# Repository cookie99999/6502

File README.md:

These are the relevant files for my ongoing WDC 65C816 based homebrew computer. It started off pretty similar to Ben Eater's 65C02 computer, but I've made significant changes since then and will continue to do so.

## Current Specs:
- WDC 65C816 clocked at 4MHz (reasonably stable at 6MHz, fails to boot at 8 likely due to slow memory/logic)
- 512K SRAM
- 8K NOR flash accessible to the user
- 2 6522 VIAs providing 2 8-bit GPIO ports and a couple timers and shift registers each
- 6551 ACIA UART for serial I/O. Rockwell part works only up to about 4MHz, but avoids the TX empty flag bug of the WDC part
- PS/2 interface provided by ATTiny26L on one of the VIA ports
- CompactFlash storage (via PATA adapter)
- VGA video output from a Pi Pico 2 providing text display and (very slow) bitmapped graphics
- expensive and oversized 4-layer PCB

## To do list:
- Bitbang an SPI RTC on a remaining VIA port
- possibly look into sound and/or joysticks on the other 2
- new PCB layout using more SMD/PLCC parts to reduce size and cost, with more SRAM and a proper DE-9 serial port

I've used and modified ideas from many sources, notably Ben Eater, Garth Wilson, Daryl Rictor, Grant Searle, and many users and articles on the 6502.org forum.

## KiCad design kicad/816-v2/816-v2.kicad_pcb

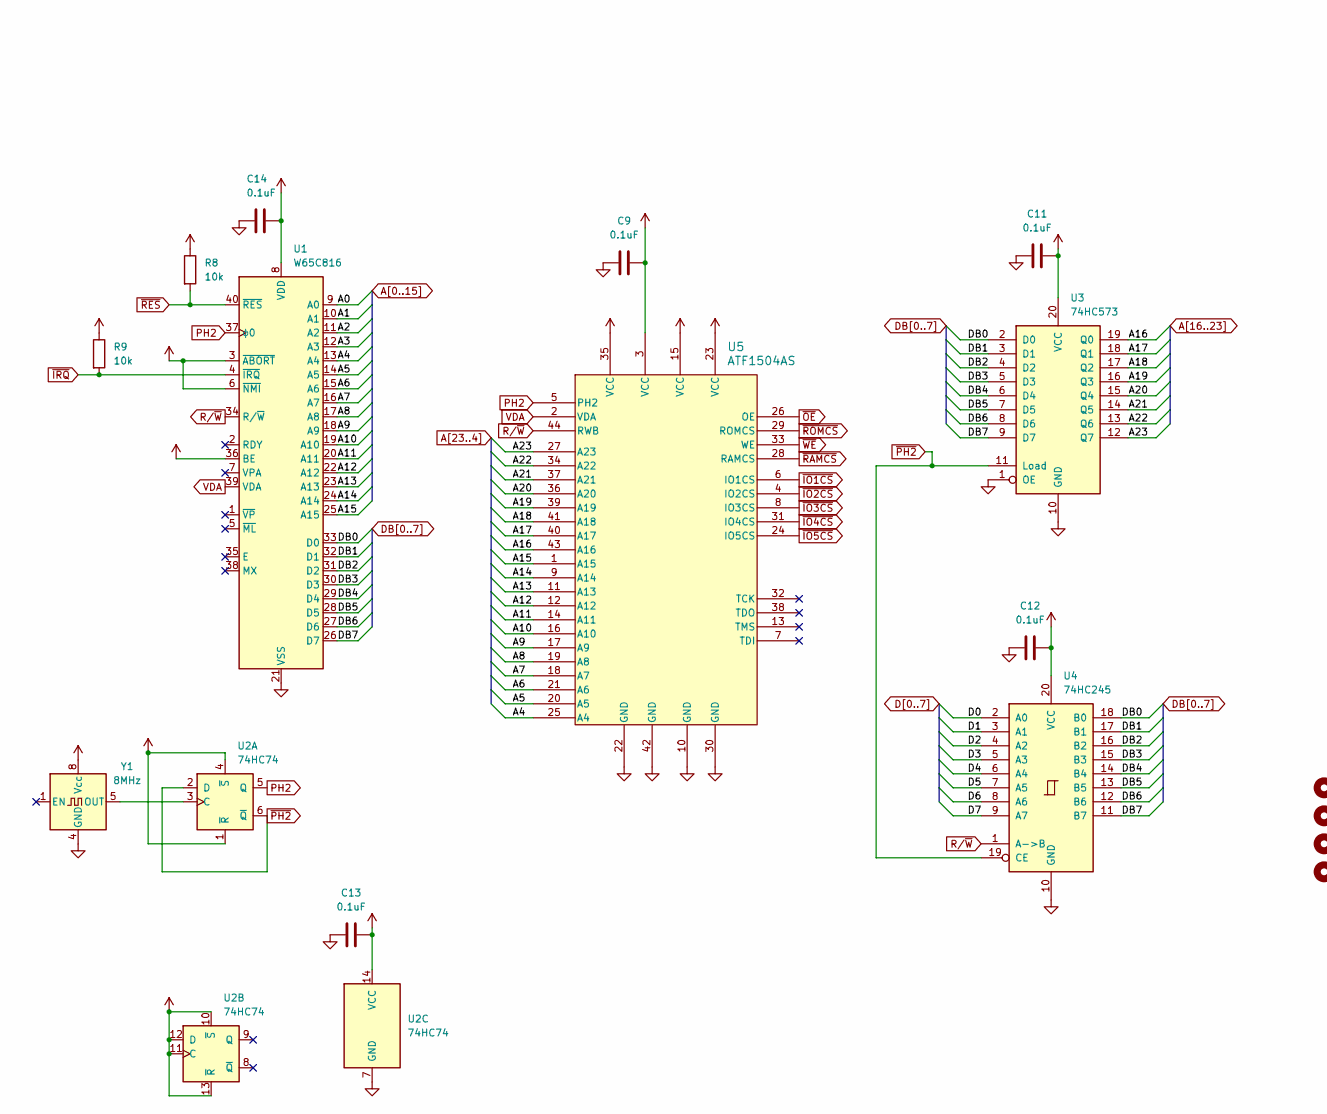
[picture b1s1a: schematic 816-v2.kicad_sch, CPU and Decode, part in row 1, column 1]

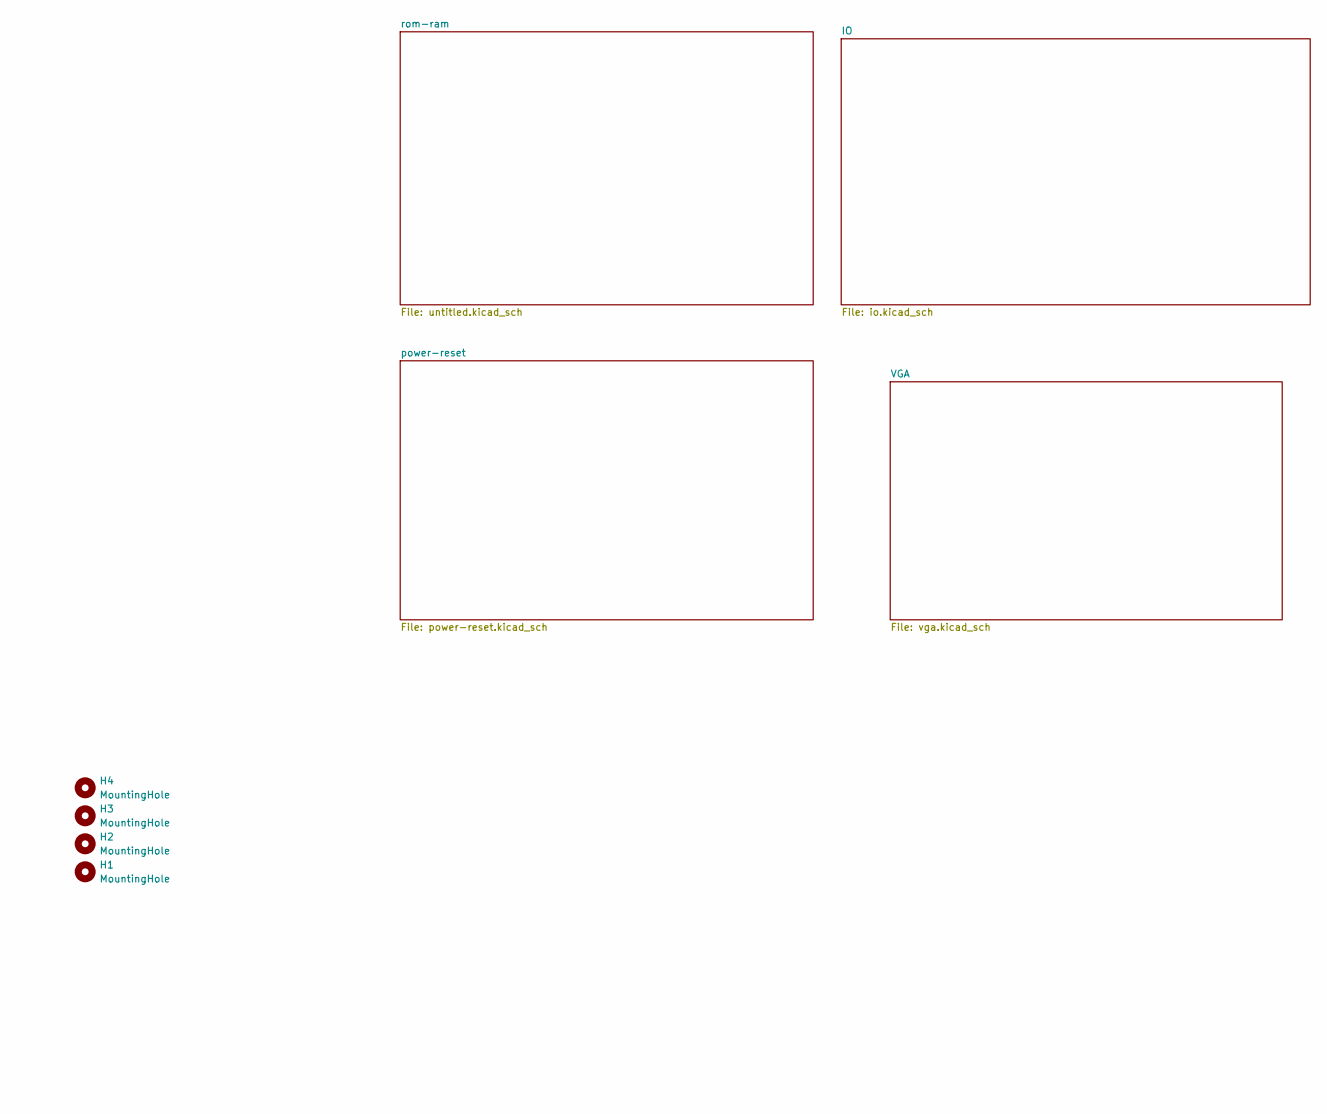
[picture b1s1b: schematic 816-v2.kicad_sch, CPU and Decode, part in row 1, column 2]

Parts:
C9, C11, C12, C13, C14: 0.1uF; C_Disc_D4.3mm_W1.9mm_P5.00mm
H1, H2, H3, H4: MountingHole; MountingHole_3.2mm_M3
R8, R9: 10k; R_Axial_DIN0207_L6.3mm_D2.5mm_P7.62mm_Horizontal
U1: W65C816; DIP-40_W15.24mm_Socket
U2: 74HC74; DIP-14_W7.62mm_Socket
U3: 74HC573; DIP-20_W7.62mm_Socket
U4: 74HC245; DIP-20_W7.62mm_Socket
U5: ATF1504AS; PLCC-44_THT-Socket
Y1: 8MHz; DIP-8_W7.62mm_Socket

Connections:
A0: U1.9 (A0); also elsewhere on the board
A1: U1.10 (A1); also elsewhere on the board
A2: U1.11 (A2); also elsewhere on the board
A3: U1.12 (A3); also elsewhere on the board
A4: U1.13 (A4), U5.25 (A4); also elsewhere on the board
A5: U1.14 (A5), U5.20 (A5); also elsewhere on the board
A6: U1.15 (A6), U5.21 (A6); also elsewhere on the board
A7: U1.16 (A7), U5.18 (A7); also elsewhere on the board
A8: U1.17 (A8), U5.19 (A8); also elsewhere on the board
A9: U1.18 (A9), U5.17 (A9); also elsewhere on the board
A10: U1.19 (A10), U5.16 (A10); also elsewhere on the board
A11: U1.20 (A11), U5.14 (A11); also elsewhere on the board
A12: U1.22 (A12), U5.12 (A12); also elsewhere on the board
A13: U1.23 (A13), U5.11 (A13); also elsewhere on the board
A14: U1.24 (A14), U5.9 (A14); also elsewhere on the board
A15: U1.25 (A15), U5.1 (A15); also elsewhere on the board
A16: U3.19 (Q0), U5.43 (A16); also elsewhere on the board
A17: U3.18 (Q1), U5.40 (A17); also elsewhere on the board
A18: U3.17 (Q2), U5.41 (A18); also elsewhere on the board
A19: U3.16 (Q3), U5.39 (A19)
A20: U3.15 (Q4), U5.36 (A20)
A21: U3.14 (Q5), U5.37 (A21)
A22: U3.13 (Q6), U5.34 (A22)
A23: U3.12 (Q7), U5.27 (A23)
D0: U4.2 (A0); also elsewhere on the board
D1: U4.3 (A1); also elsewhere on the board
D2: U4.4 (A2); also elsewhere on the board
D3: U4.5 (A3); also elsewhere on the board
D4: U4.6 (A4); also elsewhere on the board
D5: U4.7 (A5); also elsewhere on the board
D6: U4.8 (A6); also elsewhere on the board
D7: U4.9 (A7); also elsewhere on the board
DB0: U1.33 (D0), U3.2 (D0), U4.18 (B0)
DB1: U1.32 (D1), U3.3 (D1), U4.17 (B1)
DB2: U1.31 (D2), U3.4 (D2), U4.16 (B2)
DB3: U1.30 (D3), U3.5 (D3), U4.15 (B3)
DB4: U1.29 (D4), U3.6 (D4), U4.14 (B4)
DB5: U1.28 (D5), U3.7 (D5), U4.13 (B5)
DB6: U1.27 (D6), U3.8 (D6), U4.12 (B6)
DB7: U1.26 (D7), U3.9 (D7), U4.11 (B7)
GND: C9.1, C11.2, C12.2, C13.2, C14.1, U1.21 (VSS), U2.7 (GND), U3.1 (OE), U3.10 (GND), U4.10 (GND), U5.10 (GND), U5.22 (GND), U5.30 (GND), U5.42 (GND), Y1.4 (GND); also elsewhere on the board
unnamed: U2.3 (C), Y1.5 (OUT)
PH2: U1.37 (ϕ0), U2.5 (Q), U5.5 (PH2); also elsewhere on the board
R/~W: U1.34 (R/~W), U4.1 (A->B), U5.44 (RWB); also elsewhere on the board
VCC: C9.2, C11.1, C12.1, C13.1, C14.2, R8.1, R9.1, U1.3 (~ABORT), U1.6 (~NMI), U1.8 (VDD), U1.36 (BE), U2.1 (~R), U2.4 (~S), U2.10 (~S), U2.11 (C), U2.12 (D), U2.13 (~R), U2.14 (VCC), U3.20 (VCC), U4.20 (VCC), U5.3 (VCC), U5.15 (VCC), U5.23 (VCC), U5.35 (VCC), Y1.8 (Vcc); also elsewhere on the board
VDA: U1.39 (VDA), U5.2 (VDA)
~IO1CS: U5.6 (IO1CS); also elsewhere on the board
~IO2CS: U5.4 (IO2CS); also elsewhere on the board
~IO3CS: U5.8 (IO3CS); also elsewhere on the board
~IO4CS: U5.31 (IO4CS); also elsewhere on the board
~IO5CS: U5.24 (IO5CS); also elsewhere on the board
~IRQ: R9.2, U1.4 (~IRQ); also elsewhere on the board
~OE: U5.26 (OE); also elsewhere on the board
~PH2: U2.2 (D), U2.6 (~Q), U3.11 (Load), U4.19 (CE)
~RAMCS: U5.28 (RAMCS); also elsewhere on the board
~RES: R8.2, U1.40 (~RES); also elsewhere on the board
~ROMCS: U5.29 (ROMCS); also elsewhere on the board
~WE: U5.33 (WE); also elsewhere on the board

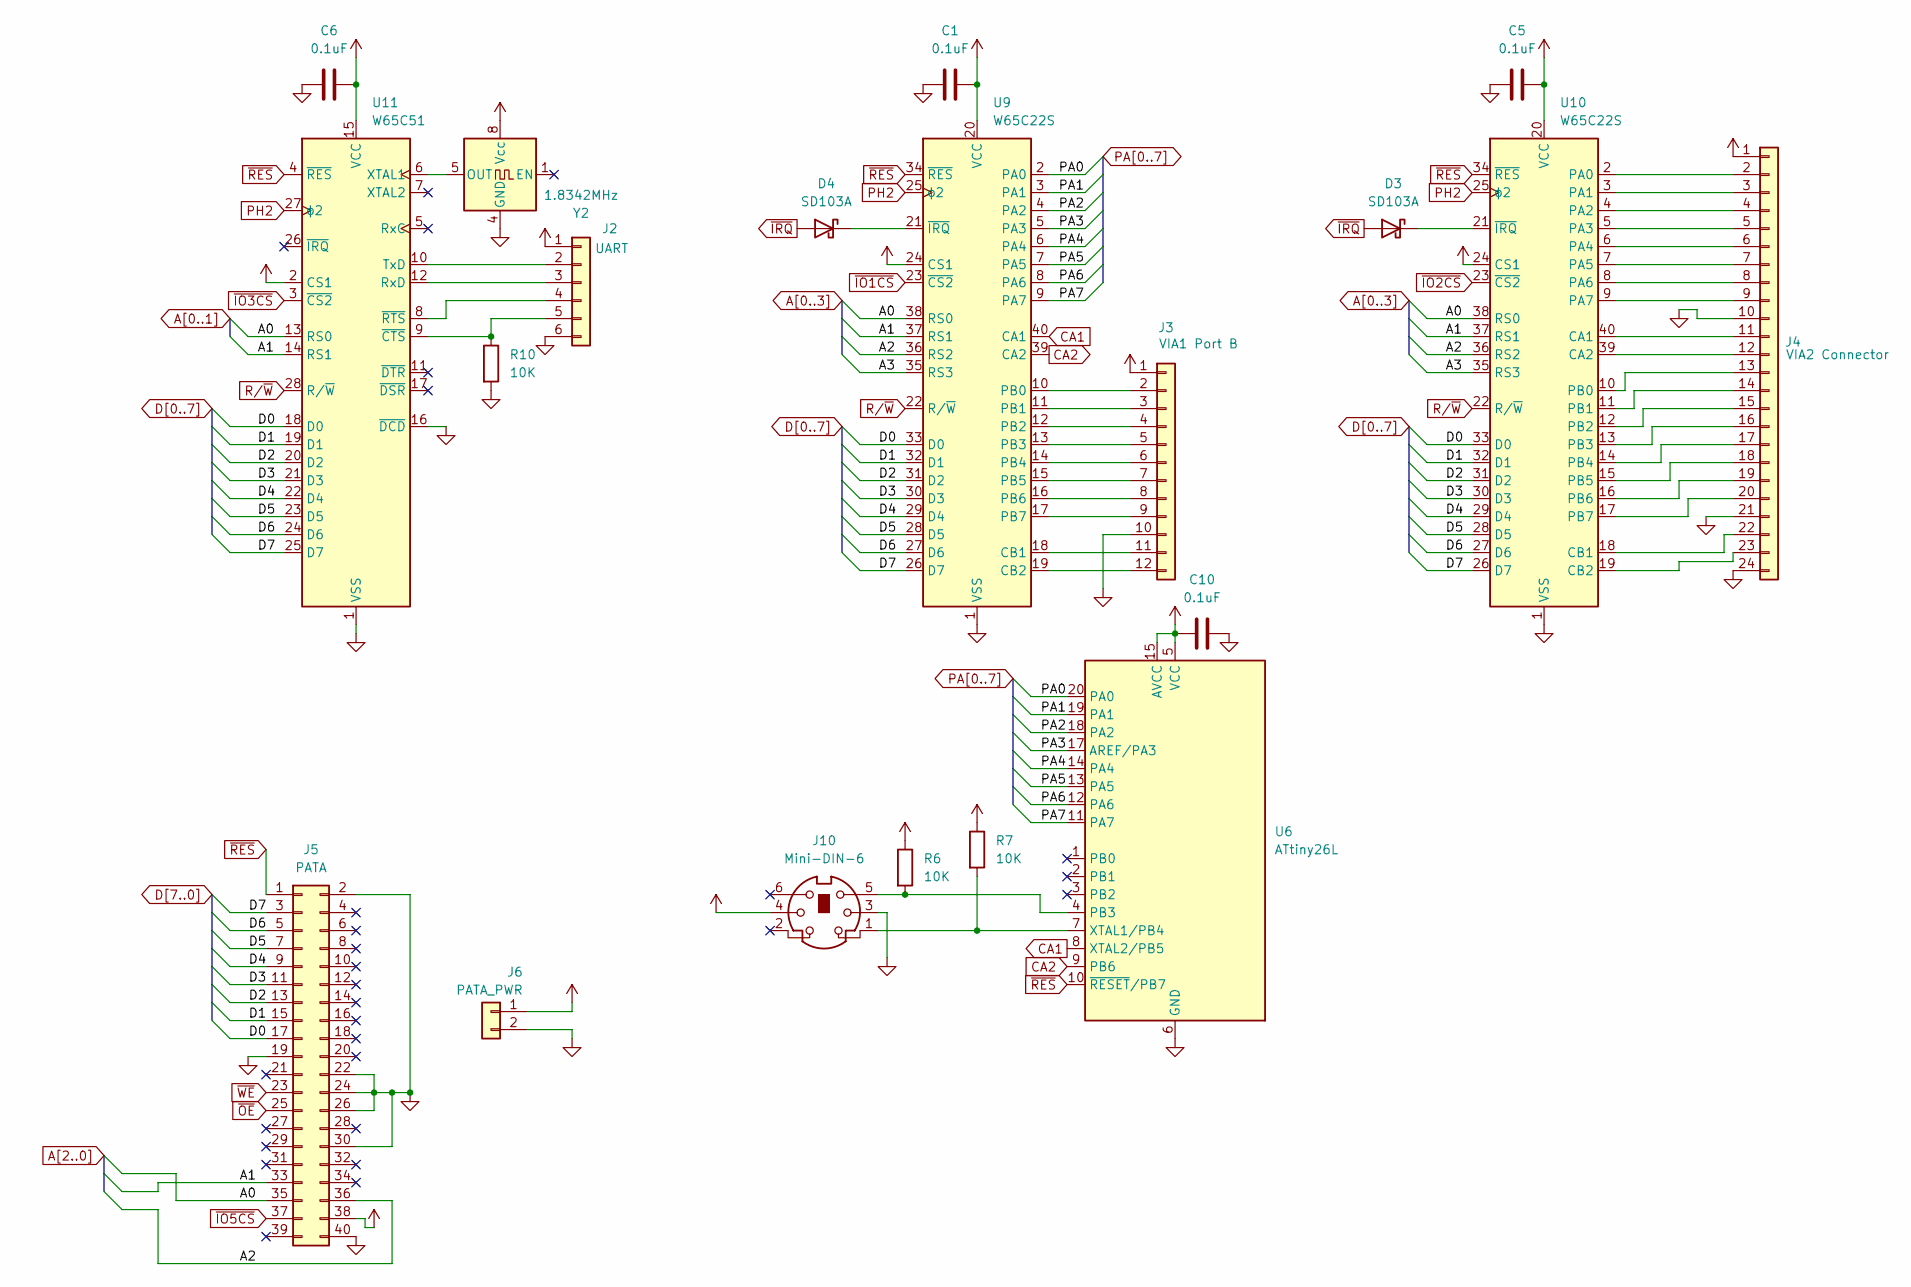
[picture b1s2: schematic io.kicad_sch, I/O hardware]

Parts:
C1, C5, C6, C10: 0.1uF; C_Disc_D4.3mm_W1.9mm_P5.00mm
D3, D4: SD103A; D_DO-35_SOD27_P7.62mm_Horizontal
J2: UART; PinHeader_1x06_P2.54mm_Vertical
J3: VIA1 Port B; PinHeader_2x06_P2.54mm_Vertical
J4: VIA2 Connector; PinHeader_2x12_P2.54mm_Vertical
J5: PATA; IDC-Header_2x20_P2.54mm_Vertical
J6: PATA_PWR; PinHeader_1x02_P2.54mm_Vertical
J10: Mini-DIN-6; TE_5749180-1
R6, R7, R10: 10K; R_Axial_DIN0207_L6.3mm_D2.5mm_P7.62mm_Horizontal
U6: ATtiny26L; DIP-20_W7.62mm_Socket
U9, U10: W65C22S; DIP-40_W15.24mm_Socket
U11: W65C51; DIP-28_W15.24mm_Socket
Y2: 1.8342MHz; Oscillator_DIP-8

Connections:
A0: J5.35, U9.38 (RS0), U10.38 (RS0), U11.13 (RS0); also elsewhere on the board
A1: J5.33, U9.37 (RS1), U10.37 (RS1), U11.14 (RS1); also elsewhere on the board
A2: J5.36, U9.36 (RS2), U10.36 (RS2); also elsewhere on the board
A3: U9.35 (RS3), U10.35 (RS3); also elsewhere on the board
CA1: U6.8 (XTAL2/PB5), U9.40 (CA1)
CA2: U6.9 (PB6), U9.39 (CA2)
D0: J5.17, U9.33 (D0), U10.33 (D0), U11.18 (D0); also elsewhere on the board
D1: J5.15, U9.32 (D1), U10.32 (D1), U11.19 (D1); also elsewhere on the board
D2: J5.13, U9.31 (D2), U10.31 (D2), U11.20 (D2); also elsewhere on the board
D3: J5.11, U9.30 (D3), U10.30 (D3), U11.21 (D3); also elsewhere on the board
D4: J5.9, U9.29 (D4), U10.29 (D4), U11.22 (D4); also elsewhere on the board
D5: J5.7, U9.28 (D5), U10.28 (D5), U11.23 (D5); also elsewhere on the board
D6: J5.5, U9.27 (D6), U10.27 (D6), U11.24 (D6); also elsewhere on the board
D7: J5.3, U9.26 (D7), U10.26 (D7), U11.25 (D7); also elsewhere on the board
GND: C1.2, C5.2, C6.2, C10.2, J2.6, J3.10, J4.10, J4.21, J4.24, J5.2, J5.19, J5.22, J5.24, J5.26, J5.30, J5.40, J6.2, J10.3, R10.2, U6.6 (GND), U6.16 (GND), U9.1 (VSS), U10.1 (VSS), U11.1 (VSS), U11.16 (~DCD), Y2.4 (GND); also elsewhere on the board
unnamed: D3.1 (K), U10.21 (~IRQ)
unnamed: D4.1 (K), U9.21 (~IRQ)
unnamed: J2.2, U11.10 (TxD)
unnamed: J2.3, U11.12 (RxD)
unnamed: J2.4, U11.8 (~RTS)
unnamed: J2.5, R10.1, U11.9 (~CTS)
unnamed: J3.2, U9.10 (PB0)
unnamed: J3.3, U9.11 (PB1)
unnamed: J3.4, U9.12 (PB2)
unnamed: J3.5, U9.13 (PB3)
unnamed: J3.6, U9.14 (PB4)
unnamed: J3.7, U9.15 (PB5)
unnamed: J3.8, U9.16 (PB6)
unnamed: J3.9, U9.17 (PB7)
unnamed: J3.11, U9.18 (CB1)
unnamed: J3.12, U9.19 (CB2)
unnamed: J4.2, U10.2 (PA0)
unnamed: J4.3, U10.3 (PA1)
unnamed: J4.4, U10.4 (PA2)
unnamed: J4.5, U10.5 (PA3)
unnamed: J4.6, U10.6 (PA4)
unnamed: J4.7, U10.7 (PA5)
unnamed: J4.8, U10.8 (PA6)
unnamed: J4.9, U10.9 (PA7)
unnamed: J4.11, U10.40 (CA1)
unnamed: J4.12, U10.39 (CA2)
unnamed: J4.13, U10.10 (PB0)
unnamed: J4.14, U10.11 (PB1)
unnamed: J4.15, U10.12 (PB2)
unnamed: J4.16, U10.13 (PB3)
unnamed: J4.17, U10.14 (PB4)
unnamed: J4.18, U10.15 (PB5)
unnamed: J4.19, U10.16 (PB6)
unnamed: J4.20, U10.17 (PB7)
unnamed: J4.22, U10.18 (CB1)
unnamed: J4.23, U10.19 (CB2)
unnamed: J10.5, R6.2, U6.4 (PB3)
unnamed: J10.1, R7.2, U6.7 (XTAL1/PB4)
unnamed: U11.6 (XTAL1), Y2.5 (OUT)
PA0: U6.20 (PA0), U9.2 (PA0)
PA1: U6.19 (PA1), U9.3 (PA1)
PA2: U6.18 (PA2), U9.4 (PA2)
PA3: U6.17 (AREF/PA3), U9.5 (PA3)
PA4: U6.14 (PA4), U9.6 (PA4)
PA5: U6.13 (PA5), U9.7 (PA5)
PA6: U6.12 (PA6), U9.8 (PA6)
PA7: U6.11 (PA7), U9.9 (PA7)
PH2: U9.25 (ϕ2), U10.25 (ϕ2), U11.27 (ϕ2); also elsewhere on the board
R/~W: U9.22 (R/~W), U10.22 (R/~W), U11.28 (R/~W); also elsewhere on the board
VCC: C1.1, C5.1, C6.1, C10.1, J2.1, J3.1, J4.1, J5.38, J6.1, J10.4, R6.1, R7.1, U6.5 (VCC), U6.15 (AVCC), U9.20 (VCC), U9.24 (CS1), U10.20 (VCC), U10.24 (CS1), U11.2 (CS1), U11.15 (VCC), Y2.8 (Vcc); also elsewhere on the board
~IO1CS: U9.23 (~CS2); also elsewhere on the board
~IO2CS: U10.23 (~CS2); also elsewhere on the board
~IO3CS: U11.3 (~CS2); also elsewhere on the board
~IO5CS: J5.37; also elsewhere on the board
~IRQ: D3.2 (A), D4.2 (A); also elsewhere on the board
~OE: J5.25; also elsewhere on the board
~RES: J5.1, U6.10 (~RESET/PB7), U9.34 (~RES), U10.34 (~RES), U11.4 (~RES); also elsewhere on the board
~WE: J5.23; also elsewhere on the board

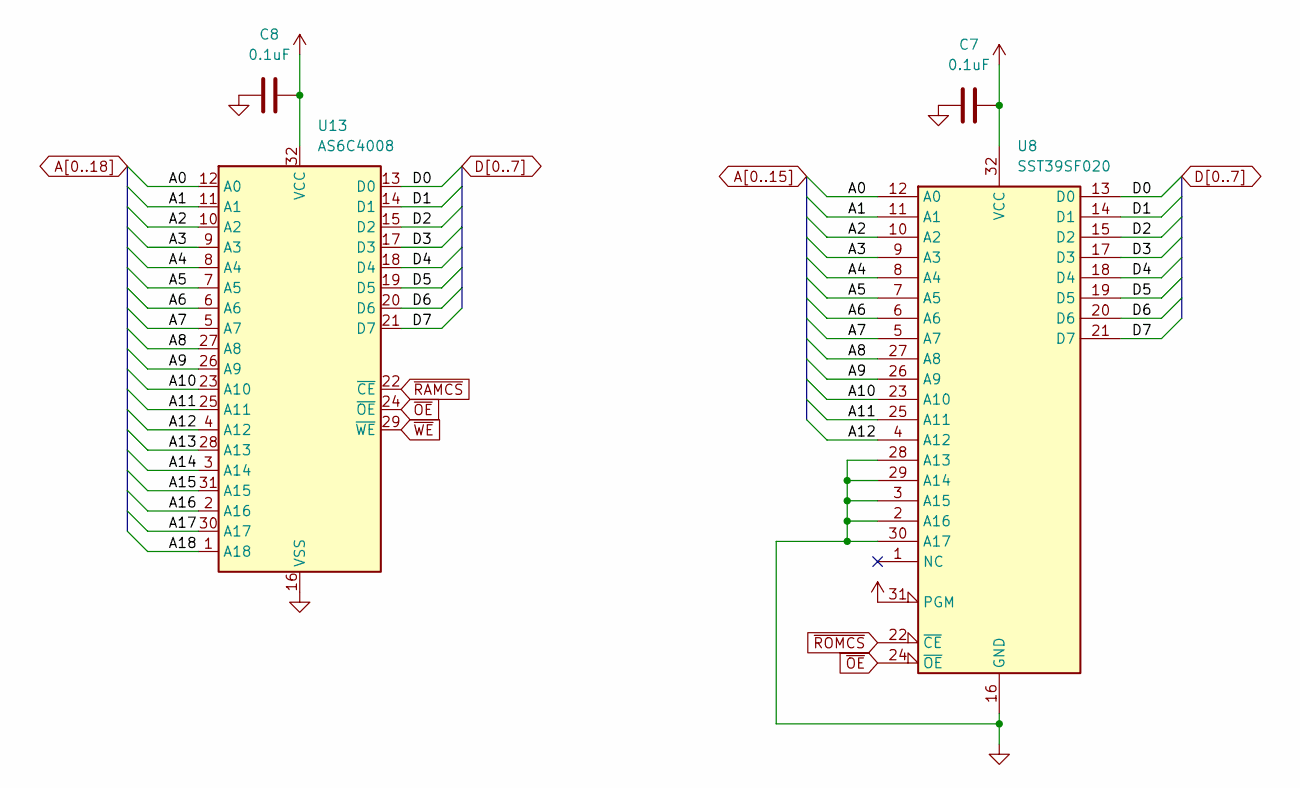
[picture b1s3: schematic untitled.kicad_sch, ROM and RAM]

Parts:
C7, C8: 0.1uF; C_Disc_D4.3mm_W1.9mm_P5.00mm
U8: SST39SF020; DIP-32_W15.24mm_Socket
U13: AS6C4008; DIP-32_W15.24mm_Socket

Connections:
A0: U8.12 (A0), U13.12 (A0); also elsewhere on the board
A1: U8.11 (A1), U13.11 (A1); also elsewhere on the board
A2: U8.10 (A2), U13.10 (A2); also elsewhere on the board
A3: U8.9 (A3), U13.9 (A3); also elsewhere on the board
A4: U8.8 (A4), U13.8 (A4); also elsewhere on the board
A5: U8.7 (A5), U13.7 (A5); also elsewhere on the board
A6: U8.6 (A6), U13.6 (A6); also elsewhere on the board
A7: U8.5 (A7), U13.5 (A7); also elsewhere on the board
A8: U8.27 (A8), U13.27 (A8); also elsewhere on the board
A9: U8.26 (A9), U13.26 (A9); also elsewhere on the board
A10: U8.23 (A10), U13.23 (A10); also elsewhere on the board
A11: U8.25 (A11), U13.25 (A11); also elsewhere on the board
A12: U8.4 (A12), U13.4 (A12); also elsewhere on the board
A13: U13.28 (A13); also elsewhere on the board
A14: U13.3 (A14); also elsewhere on the board
A15: U13.31 (A15); also elsewhere on the board
A16: U13.2 (A16); also elsewhere on the board
A17: U13.30 (A17); also elsewhere on the board
A18: U13.1 (A18); also elsewhere on the board
D0: U8.13 (D0), U13.13 (D0); also elsewhere on the board
D1: U8.14 (D1), U13.14 (D1); also elsewhere on the board
D2: U8.15 (D2), U13.15 (D2); also elsewhere on the board
D3: U8.17 (D3), U13.17 (D3); also elsewhere on the board
D4: U8.18 (D4), U13.18 (D4); also elsewhere on the board
D5: U8.19 (D5), U13.19 (D5); also elsewhere on the board
D6: U8.20 (D6), U13.20 (D6); also elsewhere on the board
D7: U8.21 (D7), U13.21 (D7); also elsewhere on the board
GND: C7.2, C8.2, U8.2 (A16), U8.3 (A15), U8.16 (GND), U8.28 (A13), U8.29 (A14), U8.30 (A17), U13.16 (VSS); also elsewhere on the board
VCC: C7.1, C8.1, U8.31 (PGM), U8.32 (VCC), U13.32 (VCC); also elsewhere on the board
~OE: U8.24 (~OE), U13.24 (~OE); also elsewhere on the board
~RAMCS: U13.22 (~CE); also elsewhere on the board
~ROMCS: U8.22 (~CE); also elsewhere on the board
~WE: U13.29 (~WE); also elsewhere on the board

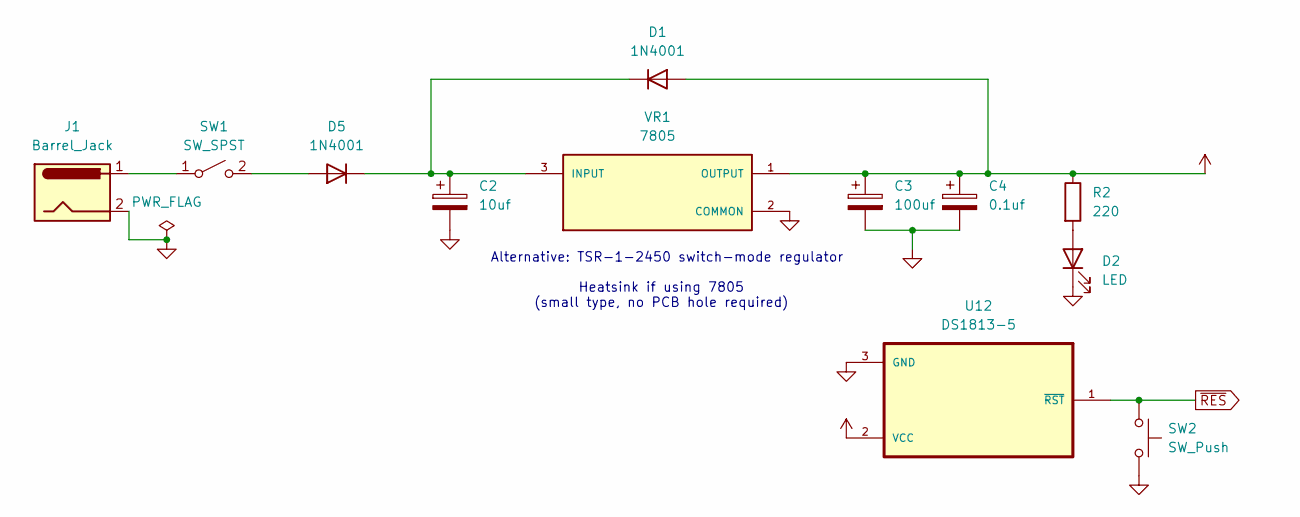
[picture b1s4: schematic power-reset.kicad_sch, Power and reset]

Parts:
C2: 10uf; CP_Radial_D5.0mm_P2.50mm
C3: 100uf; CP_Radial_D5.0mm_P2.50mm
C4: 0.1uf; C_Disc_D4.3mm_W1.9mm_P5.00mm
D1, D5: 1N4001; D_DO-41_SOD81_P10.16mm_Horizontal
D2: LED; LED_D5.0mm
J1: Barrel_Jack; BarrelJack_Horizontal
R2: 220; R_Axial_DIN0207_L6.3mm_D2.5mm_P7.62mm_Horizontal
SW1: SW_SPST; SW_Slide_SPDT_Straight_CK_OS102011MS2Q
SW2: SW_Push; SW_PUSH_6mm
U12: DS1813-5; TO-92L
VR1: 7805; TO-220-3_Vertical; PARTREV V

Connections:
GND: C2.2, C3.2, C4.2, D2.1 (K), J1.2, SW2.2, U12.3 (GND), VR1.2 (COMMON); also elsewhere on the board
unnamed: C2.1, D1.1 (K), D5.1 (K), VR1.3 (INPUT)
unnamed: D2.2 (A), R2.2
unnamed: D5.2 (A), SW1.2 (B)
unnamed: J1.1, SW1.1 (A)
VCC: C3.1, C4.1, D1.2 (A), R2.1, U12.2 (VCC), VR1.1 (OUTPUT); also elsewhere on the board
~RES: SW2.1, U12.1 (~RST); also elsewhere on the board

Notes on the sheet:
Heatsink if using 7805 (small type, no PCB hole required)
Alternative: TSR-1-2450 switch-mode regulator

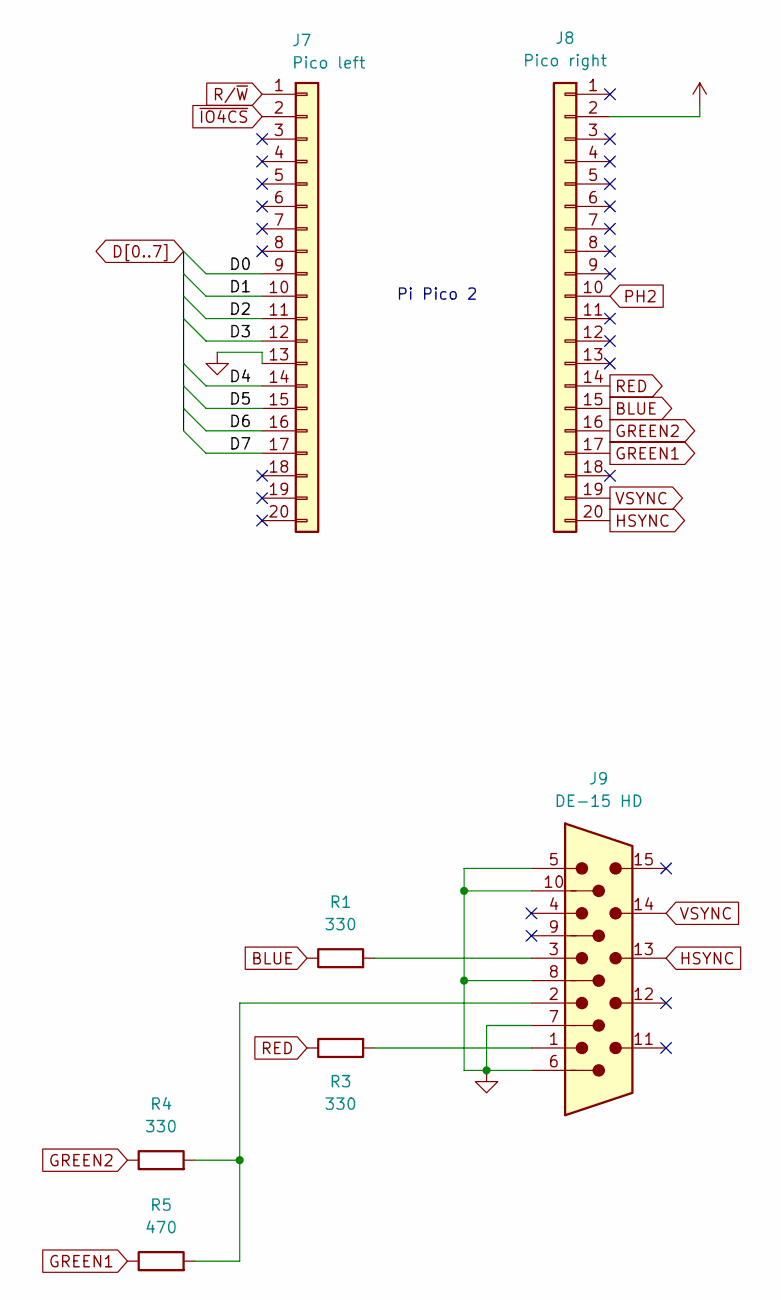
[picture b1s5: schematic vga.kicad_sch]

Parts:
J7: Pico left; PinHeader_1x20_P2.54mm_Vertical
J8: Pico right; PinHeader_1x20_P2.54mm_Vertical
J9: DE-15 HD; AMPHENOL_ICD15S13E4GV00LF
R1, R3, R4: 330; R_Axial_DIN0207_L6.3mm_D2.5mm_P7.62mm_Horizontal
R5: 470; R_Axial_DIN0207_L6.3mm_D2.5mm_P7.62mm_Horizontal

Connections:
BLUE: J8.15, R1.1
D0: J7.9; also elsewhere on the board
D1: J7.10; also elsewhere on the board
D2: J7.11; also elsewhere on the board
D3: J7.12; also elsewhere on the board
D4: J7.14; also elsewhere on the board
D5: J7.15; also elsewhere on the board
D6: J7.16; also elsewhere on the board
D7: J7.17; also elsewhere on the board
GND: J7.13, J9.5, J9.6, J9.7, J9.8, J9.10; also elsewhere on the board
GREEN1: J8.17, R5.1
GREEN2: J8.16, R4.1
HSYNC: J8.20, J9.13
unnamed: J9.1, R3.2
unnamed: J9.2, R4.2, R5.2
unnamed: J9.3, R1.2
PH2: J8.10; also elsewhere on the board
RED: J8.14, R3.1
R/~W: J7.1; also elsewhere on the board
VCC: J8.2; also elsewhere on the board
VSYNC: J8.19, J9.14
~IO4CS: J7.2; also elsewhere on the board

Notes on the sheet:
Pi Pico 2

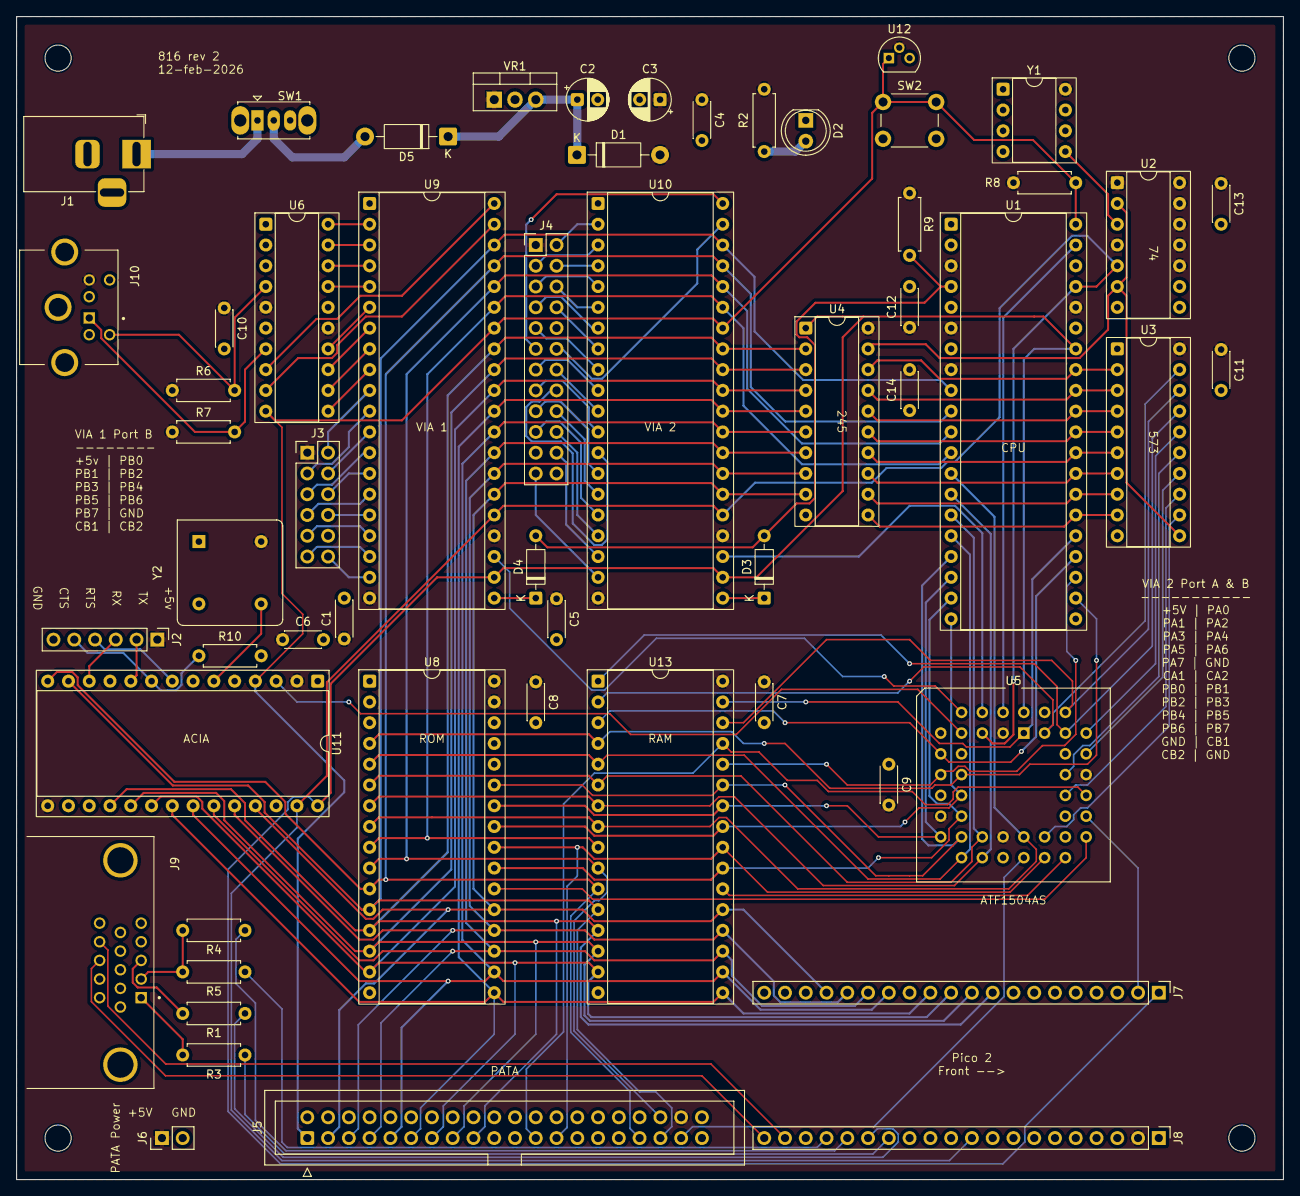
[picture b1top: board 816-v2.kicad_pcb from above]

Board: 4 copper layers, 154.9 x 142.2 mm, 60 parts (0 on the bottom side), 120 nets.

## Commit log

2024-03-06 Begin work on Forth implementation
2024-03-07 work on macros
2024-03-07 Implement several more words
2024-09-30 Begin work on emulator
2024-10-02 Finish opcode table, begin work on decoding
2024-10-05 Add control flow instructions and debug info
2024-10-05 Add flag instructions
2024-10-05 Add stack instructions
2024-10-07 Add remaining logic instructions
2024-10-07 Add load/store instructions
2024-10-07 Add transfer instructions
2024-10-08 Add shift/rotate instructions
2024-10-08 Add arithmetic instructions
2024-10-15 Add inc/dec instructions
2024-10-15 Small bugfixes and debug code
2024-10-15 Fix instruction table for NMOS chips
2024-10-15 Rename some files for clarity
2024-10-17 Adjust memory map for eventual ACIA
2024-10-22 wozmon and basic attempts
2024-10-26 Fix V flag bug in ADC
2024-10-26 Actually fixed it this time, probably
2024-10-27 start IL for tinybasic attempt
2024-10-28 Work on IL implementation
2024-11-01 Continue implementing and testing IL prototype
2024-11-01 Working on INSRT
2024-11-01 Fix errors in debug printing, SBC, and RTI
2024-11-02 Slow work on INSRT
2024-11-03 Continue work on INSRT
2024-11-07 Continue INSRT even more
2024-11-08 Port monitor to UART I/O and add improvements
2024-11-08 Fix indentation
2024-11-08 Implement Xmodem support
2024-11-08 Range option for peek
2024-11-08 Multi byte support for poke
2024-11-08 Minor fixes
2024-11-09 Simple memory map for RAM based programs
2024-11-09 Fix poking, peeking, and xmodem
2024-12-17 Many tiny bug fixes in emulator
2024-12-18 Indentation fixed again, add some illegal opcodes
2024-12-19 Fix cycle counting, add remaining illegal opcodes Now passes nestest, however there are a few minor differences in the log relating to the prior contents of ram. Maybe related to initialization?
2024-12-19 Minor debug tweak
2024-12-19 Stray comments
2024-12-23 Testing
2024-12-24 More boilerplate
2024-12-26 Implement basic utility functions in cpu
2024-12-26 Disassembly function WIP
2024-12-28 step wip
2025-01-05 running
2025-01-05 Finished (probably) debugging legal opcodes
2025-01-05 Finish all opcodes. Passes nestest Now has feature parity with cpp version
2025-01-05 Parse iNES header
2025-01-06 ppu boilerplate
2025-01-06 Clear some warnings
2025-01-06 Drawing whole tiles
2025-01-06 Fix branching bug and JAM mnemonic
2025-01-06 Separate pattern table viewer into its own window
2025-01-10 Switch to accelerated texture rendering, fix some warns
2025-01-10 ppu wip
2025-01-17 PPU tracks cycles properly now, matches nestest
2025-01-17 Nametables appear working
2025-01-18 Draw debug windows with real palettes
2025-01-18 Fix palette mirroring
2025-01-18 Adjust nmi hack
2025-01-19 Improve sdl2 rendering speed
2025-01-19 Fixed bug with memory address mirroring
2025-01-19 Fix second address mirroring bug
2025-01-19 Implement sprite display
2025-01-20 Hack to make galaxian boot
2025-01-20 Remove old cpp code
2025-01-20 Fixed bug in palette read/write that was corrupting CHR
2025-02-26 Clean up junk/test programs
2025-02-26 Address decoders for galette and WinCUPL
2025-02-28 Adjust for 65816, fix xmodem receive
2025-02-28 Test program for working on xmodem
2025-03-08 Move xmodem code into its own file. XMODEM/CRC receive now works perfectly.
2025-03-08 Minor fixes and adjustments
2025-03-08 Starting fixed point mandelbrot + math routines
2025-03-08 Minor fixes and improvements
2025-03-09 Possibly fixed fixed-point adjustment
2025-03-09 Temporary code for testing
2025-03-10 Finally got fixed point mandelbrot working
2025-04-14 First draft of new address decoding
2025-04-19 Fix GAL files
2025-04-19 Update hardware addresses
2025-04-19 New ld config for larger ROM
2025-09-08 Update memory map and add IRQ OR'ing to himem PLD
2025-09-08 Update memory map
2025-09-08 Separate out xmodem from bios code, switch to buffered IRQ based input (doesn't work great and might revert)
2025-09-08 Move emulator stuff out to its own repo
2025-09-08 Clean out old/unused files
2025-09-08 Update memory map text file
2025-09-08 More cleanup
2025-09-08 Upload current Kicad files
2025-09-09 Add photo of current proto board layout
    Upper left is a PCB for the power and reset circuitry that I designed in order to practice KiCad
2025-12-18 Add pico 2 vga code and updated mandelbrot demo
2026-01-04 Switch to VGA+PS/2 for I/O, add Xmodem send command
2026-01-09 Add time-of-day counter on VIA1
2026-01-09 Add blinking cursor, text scrolling, and properly separated modes to VGA controller
2026-01-09 Minor fixes/edits to bios
2026-01-12 Add Compact Flash test
2026-01-12 Change from macros to actual subroutines
2026-01-12 Factor out wait routines, add read sector routine
2026-01-20 Switch to 16-color VGA + small cleanups
2026-01-20 Update KiCad files to get ready for PCB design
2026-01-31 CPLD files for new board
2026-01-31 Further FAT16 work
2026-01-31 Backspace support + minor edits
2026-01-31 Upload fat16.inc
2026-01-31 Update KiCad files
2026-02-12 Update KiCad files new pcb revision, hopefully working
2026-02-12 Minor zeropage usage edits
2026-02-12 More FAT16 progress
2026-02-12 Update ATF1504 logic to reflect new schematics
2026-02-15 Rename pico files
2026-02-15 Finish FAT pwd/cd type routines
2026-02-16 Addfile loading routine
2026-03-01 Update CF code for on-bus PCB version
2026-03-02 Fix address decoder more rigorous hiram testing may be required to ensure we aren't getting spurious writes
2026-03-02 Update KiCad files to reflect ROM WE bodge
2026-03-02 Fix bug in xmodem_send
2026-03-03 Minor cleanup and update documentation
2026-03-03 Add PRNG, clean up and rearrange zeropage
2026-03-03 Fix typo
2026-03-21 Add low-res mode to VGA controller
2026-03-21 Conway's Game of Life demo (very slow)
2026-03-22 Boost UART speed to 19200 + rom padding change
2026-03-22 Speed up GOL by removing multiplications
2026-04-28 Start file write code
